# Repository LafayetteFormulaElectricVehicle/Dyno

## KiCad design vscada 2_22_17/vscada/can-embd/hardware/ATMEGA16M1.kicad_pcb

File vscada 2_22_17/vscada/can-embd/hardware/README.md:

# LFEV 2015 CAN Communications Microprocessor #
This software is written for a CAN 2.0 communications board. The is a microcontroller was designed to interface all low level analog and digital sensors present on the 2015 LFEV with the main Data Acquisition Computer (SCADA). The software is capable of handling both reading and writing data.  

## Target Device ##
This software is written for the **Atmel ATMEGA 16M1 Automotive AVR**  
  
This device was selected for its price, software availability, documentation and onboard CAN bus support.

### Features ###

* Atmel® AVR® 8-bit microcontroller
* Up to 1 MIPS throughput per MHz
* 16KBytes flash of in-system programmable program memory
* 512B of in-system programmable EEPROM
* 1KBytes internal SRAM
* On-chip debug interface (debugWIRE)
* CAN 2.0A/B with six message objects - ISO 16845 certified
* Variable PWM duty cycle and frequency
* Synchronous update of all PWM registers
* Peripheral features
* One 8-bit general purpose timer/counter
* One 16-bit general purpose timer/counter
* One master/slave SPI serial interface
* 10-bit ADC
	* 11 single ended channels
	* Three differential ADC channel pairs (5×, 10×, 20×, 40×)
* 10-bit DAC for variable voltage reference (comparators, ADC)
* Programmable watchdog timer with separate on-chip oscillator
* On-chip temperature sensor

### Operating Specifications ###
- Operating voltage: 2.7V - 5.5V
- Extended operating temperature:
- -40°C to +85°C
- Core speed grade:
- 0 - 8MHz @ 2.7 - 4.5V
- 0 - 16MHz @ 4.5 - 5.5V

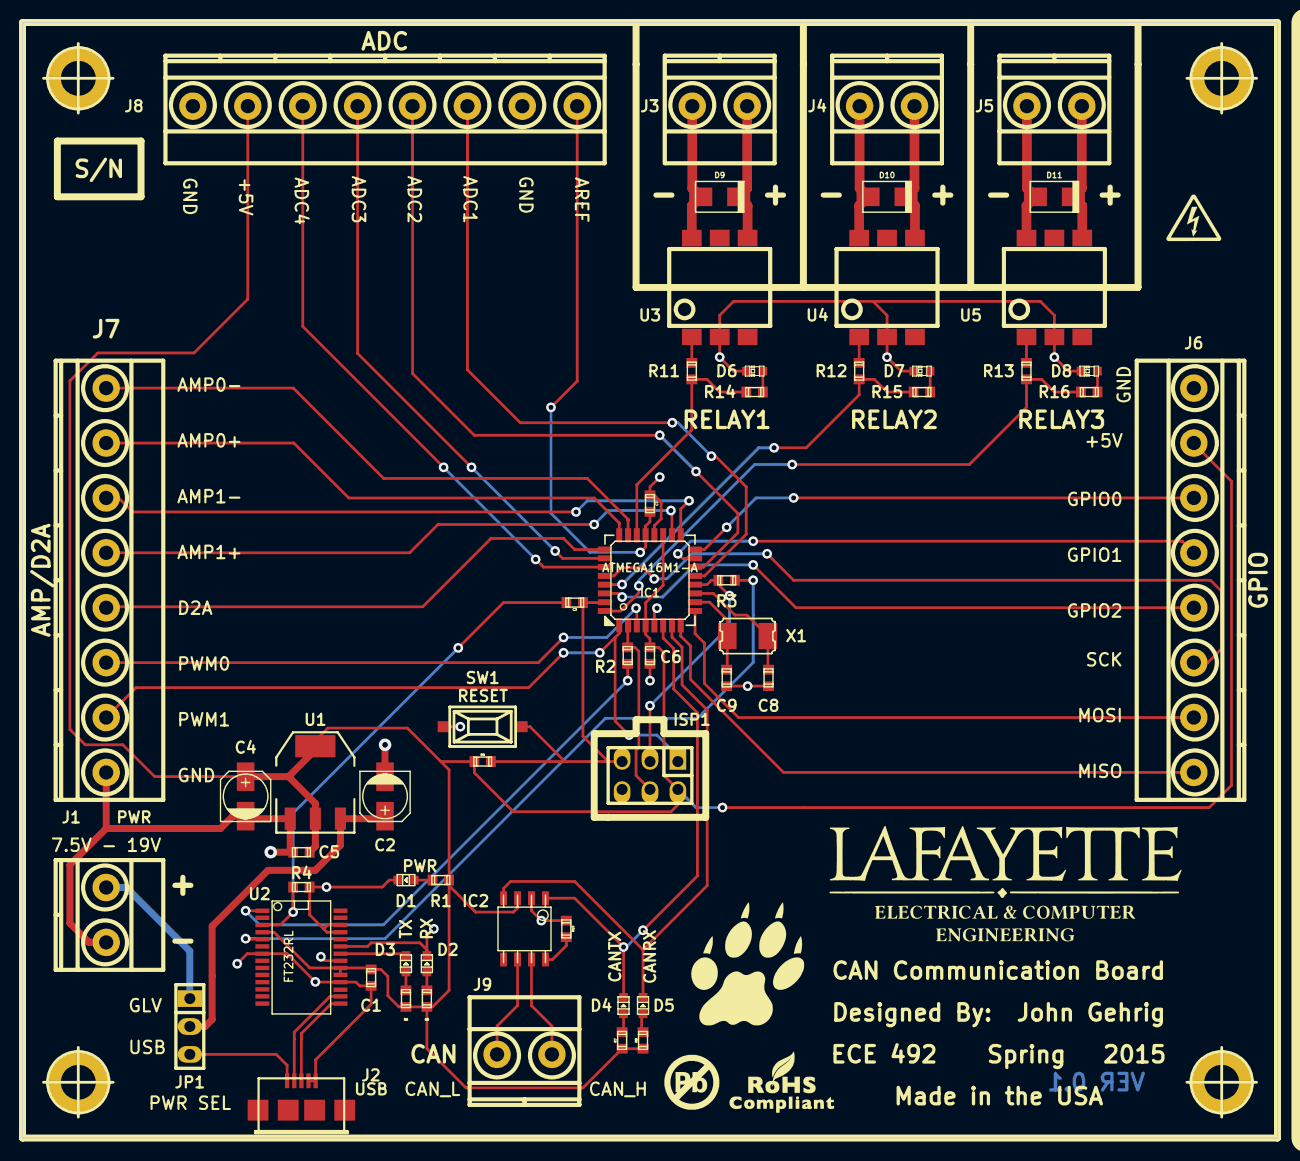
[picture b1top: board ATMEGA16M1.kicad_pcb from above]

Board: 2 copper layers, 114.3 x 101.6 mm, 60 parts (0 on the bottom side), 60 nets.

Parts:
C1: C; c_0603
C2, C4: 47u; c_elec_4x5.3
C3, C6, C7: 0.1u; c_0603
C5: 0.1; c_0603
C8, C9: 22p; c_0603
D1: PWR; Led_0603
D2: RX; Led_0603
D3: TX; Led_0603
D4: CANTX; Led_0603
D5: CANRX; Led_0603
D6: RELAY1; LED-0603
D7: RELAY2; LED-0603
D8: RELAY3; LED-0603
D9, D10, D11: DIODE; do214ac
IC1: ATMEGA16M1-A; lqfp32
IC2: MCP2551-I/SN; so-8
ISP1: ISP1; pin_strip_3x2
J1: PWR; mkds_1,5-2
J2: USB; conn_usb_B_micro_smd-2
J3: RELAY1; mkds_1,5-2
J4: RELAY2; mkds_1,5-2
J5: RELAY3; mkds_1,5-2
J6: GPIO; mkds_1,5-8
J7: AMP/D2A; mkds_1,5-8
J8: ADC; mkds_1,5-8
J9: CAN; mkds_1,5-2
JP1: JUMPER3; pin_strip_3
R1, R11, R12, R13: 220; r_0603
R2, R3, R4, R5, R6, R7, R8, R14, R15, R16: 1k; r_0603
R9, R10: 10k; r_0603
SW1: RESET; smd_push
U1: NCP1117ST50T3G; SOT223
U2: FT232RL; SSOP28
U3, U4, U5: RELAY_VO14642AT; mdip_6
X1: 16MHz; crystal_smd_5x3.2mm
hole_5mm, hole_5mm#2, hole_5mm#3, hole_5mm#4: VAL**; hole_5mm

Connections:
/ADC1: IC1.13, J8.3
/ADC2: IC1.14, J8.4
/ADC3: IC1.26, J8.5
/ADC4: IC1.27, J8.6
/AMP0+: IC1.24, J7.2
/AMP0-: IC1.23, J7.1
/AMP1+: IC1.18, J7.4
/AMP1-: IC1.17, J7.3
/AREF: C7.1, IC1.21, J8.1
/CANRX: D5.2, IC1.7, IC2.4
/CANTX: D4.2, IC1.6, IC2.1
/CAN_H: IC2.7, J9.2
/CAN_L: IC2.6, J9.1
/CBUS0: D2.2, U2.23
/CBUS1: D3.2, U2.22
/D2A: IC1.25, J7.5
/FTDI_RX: R3.1, U2.5
/FTDI_TX: R2.1, U2.1
/GPIO0: IC1.16, J6.6
/GPIO1: IC1.15, J6.5
/GPIO2: IC1.30, J6.4
/MISO: IC1.8, J6.1
/MISO_A: IC1.1, ISP1.1, J7.7
/MOSI: IC1.9, J6.2
/MOSI_A: IC1.2, ISP1.4, R2.2
/PWM0: IC1.3, J7.6
/RTS: C3.1, R4.2, U2.3
/RXD: IC1.12, ISP1.3, R3.2
/SCK: IC1.28, J6.3
/SSR0: IC1.22, R11.1, R14.2
/SSR1: IC1.29, R12.1, R15.2
/SSR2: IC1.32, R13.1, R16.2
/SSR_0A: D9.2, J3.1, U3.4
/SSR_0B: D9.1, J3.2, U3.6
/SSR_1A: D10.2, J4.1, U4.4
/SSR_1B: D10.1, J4.2, U4.6
/SSR_2A: D11.2, J5.1, U5.4
/SSR_2B: D11.1, J5.2, U5.6
/USBD+: J2.3, U2.15
/USBD-: J2.2, U2.16
/V_GLV: J1.1, JP1.1
/V_USB: J2.1, JP1.3
/V_USER: C2.1, JP1.2, U1.3
/~RESET: C3.2, IC1.31, ISP1.5, R9.1, SW1.1
GND: C1.2, C2.2, C4.2, C5.2, C6.2, C7.2, C8.2, C9.2, D1.2, D6.2, D7.2, D8.2, IC1.5, IC1.20, IC2.2, ISP1.6, J1.2, J2.4, J2.5, J6.8, J7.8, J8.2, J8.8, R4.1, R10.2, SW1.2, U1.1, U2.7, U2.18, U2.21, U2.25, U2.26, U3.2, U4.2, U5.2
unnamed: IC2.8, R10.1
unnamed: R11.2, U3.1
unnamed: R12.2, U4.1
unnamed: D6.1, R14.1
unnamed: R13.2, U5.1
unnamed: D1.1, R1.2
unnamed: D8.1, R16.1
unnamed: D7.1, R15.1
unnamed: D2.1, R5.1
unnamed: D4.1, R7.1
unnamed: D3.1, R6.1
unnamed: D5.1, R8.1
unnamed: C8.1, IC1.11, X1.1
unnamed: C9.1, IC1.10, X1.2
VCC: C1.1, C4.1, C5.1, C6.1, IC1.4, IC1.19, IC2.3, ISP1.2, J6.7, J8.7, R1.1, R5.2, R6.2, R7.2, R8.2, R9.2, U1.2, U2.4, U2.19, U2.20

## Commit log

2017-02-23 Added Original VSCADA Software
    This is the original VSCADA Software before any changes were made.
2017-02-23 Added February 16th Changes
    Added the February 16th, 2017 Changes
2017-02-23 Added Code Changed on February 22nd, 2017
    This is mostly so I have a point that I can reset to if I mess up
    anything while working today, not that I make any mistakes
    #SchmultAdvice
2017-02-23 Added attempt to change the temperature background with changes in temperature
2017-02-23 Current VSCADA Code
    Working on getting inputs over RS-232 from the power supply
